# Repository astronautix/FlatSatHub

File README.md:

# Introduction

This KiCAD project is part of the Astronautix FlatSat project, which aims to create an extensible platform for nanosatellite subsystem prototyping and experimentation.

The FlatSat platform is composed of a main metallic support plate, which can possibly host 8 submodules in star configuration. Each submodule is composed of a STM32F429IDISCOVERY board and a custom adapter hat.

All modules are hooked to a central hub  (**this project**) via a sub-d DB26HD harness. The central hub has the main purpose of routing UART signals, regulating power (dispatched via sub-d, switchable) and linking all submodules together.

# The IonSat FlatSat Hub

This is the repository to host the Flatsat central hub. 

The most important task of the FlatSat hub, aside of routing the module's signals together, is being able of handling and dispatching power. 
    
Compared to the modules, this results in a slightly more complex card layout, albeit prettier. 
The multi-level schematic also gets more intricate.

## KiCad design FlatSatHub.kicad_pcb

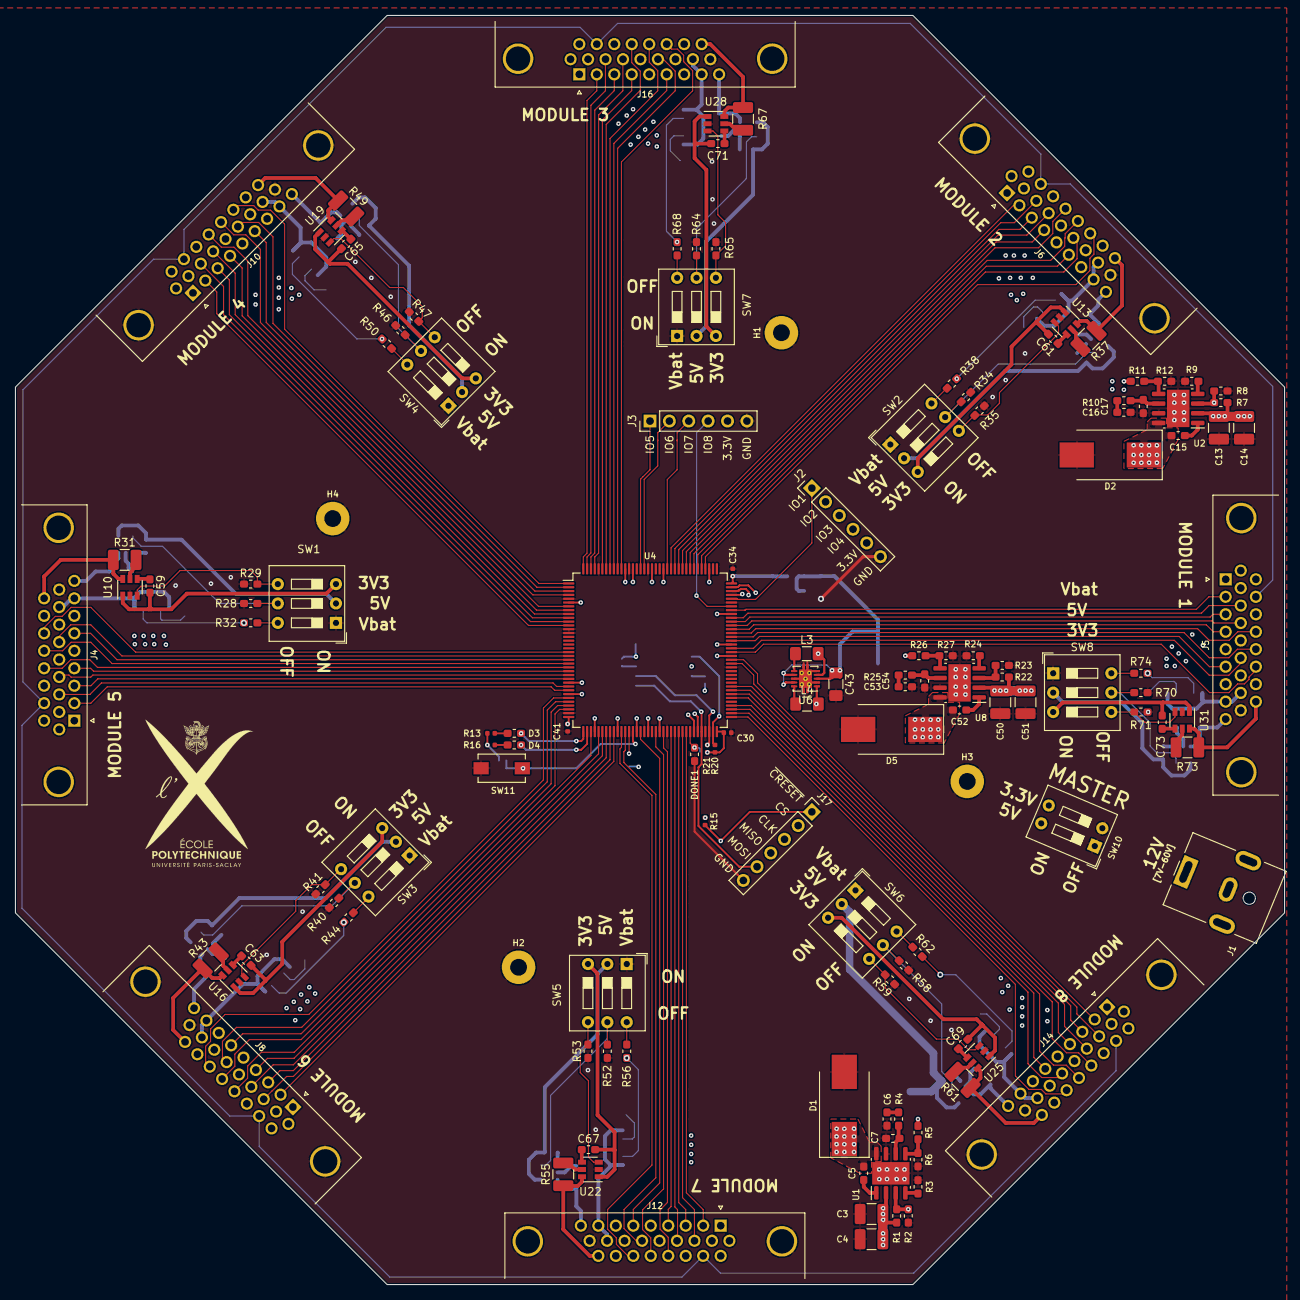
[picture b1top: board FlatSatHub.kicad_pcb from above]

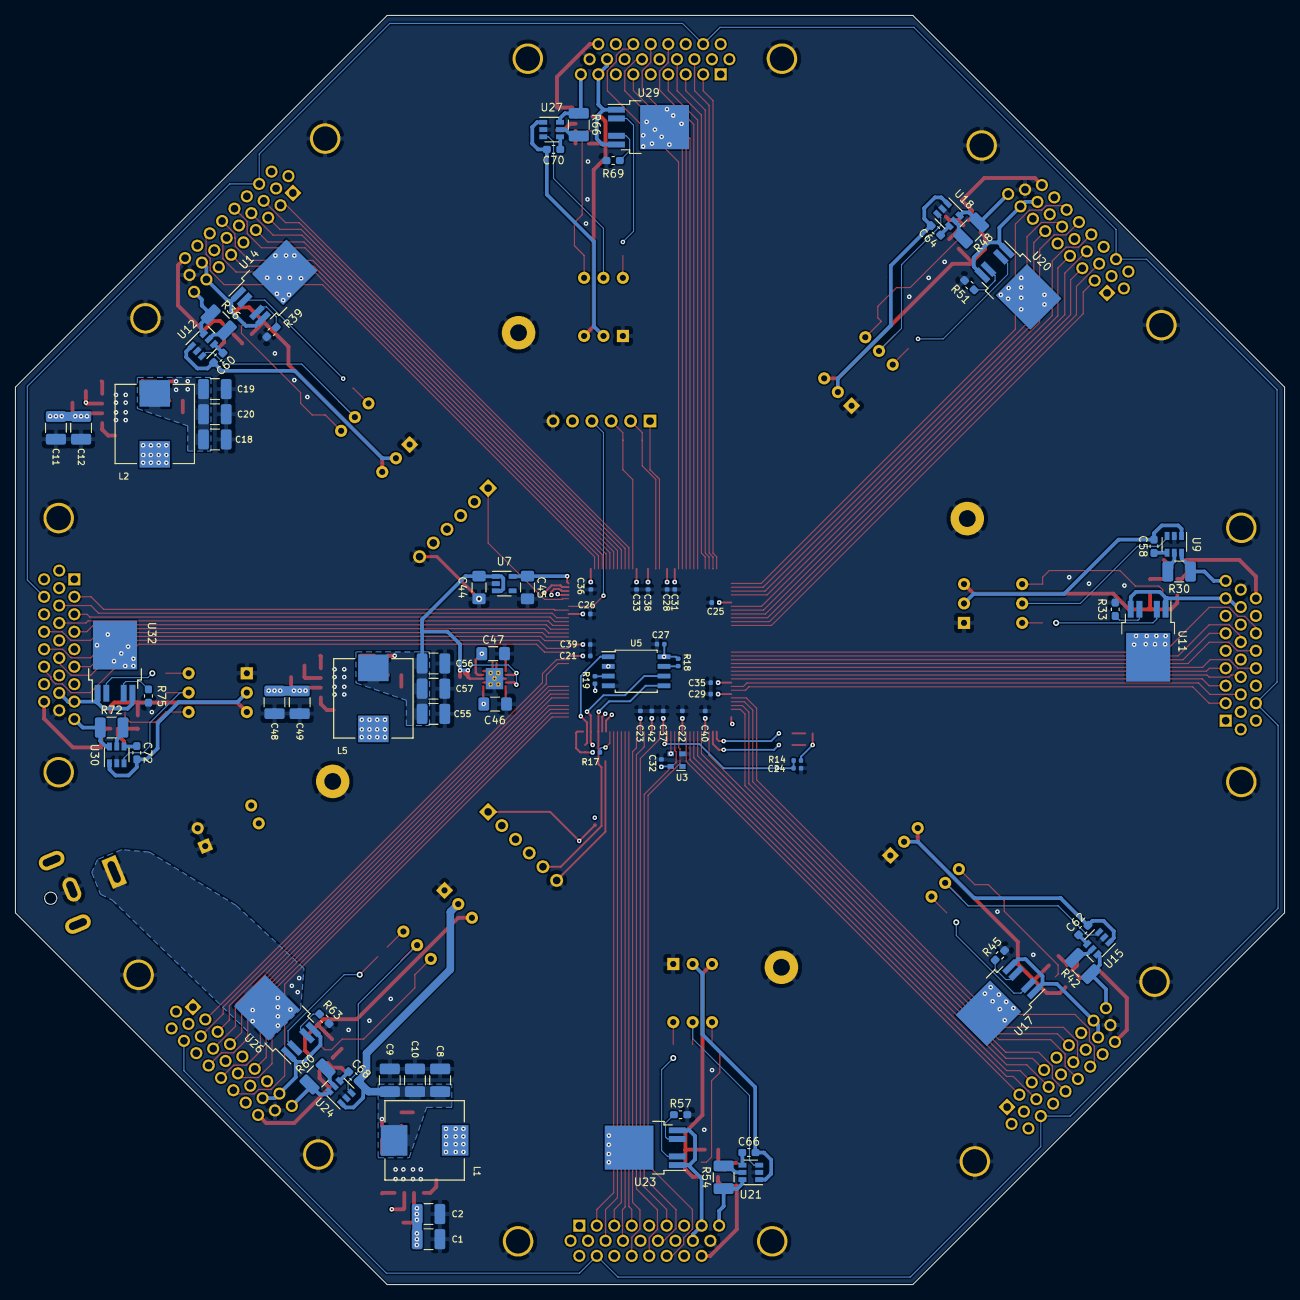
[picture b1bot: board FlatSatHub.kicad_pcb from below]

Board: 4 copper layers, 166.3 x 166.3 mm, 218 parts (88 on the bottom side), 237 nets.

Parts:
C1, C2, C3, C4, C11, C12, C13, C14, C48, C49, C50, C51: 2.2uF; C_1210_3225Metric_Pad1.42x2.65mm_HandSolder
C5, C6, C7, C15, C16, C17, C52, C53, C54, C58, C59, C60, C61, C62, C63, C64, C65, C66, C67, C68, C69, C70, C71, C72, C73: C; C_0603_1608Metric_Pad1.05x0.95mm_HandSolder
C8, C9, C10, C18, C19, C20, C55, C56, C57: 47u; C_1210_3225Metric_Pad1.42x2.65mm_HandSolder
C21, C22, C23, C24, C25, C26, C27, C28, C29, C30, C31, C32, C33, C34, C35, C36, C37, C38, C39, C40, C41, C42: 100nF; C_0402_1005Metric
C43, C44, C45, C46, C47: 10uF; C_1206_3216Metric_Pad1.42x1.75mm_HandSolder
D1, D2, D5: D_Schottky; D_SMC_Handsoldering
D3, D4: LED; R_0603_1608Metric_Pad1.05x0.95mm_HandSolder
DONE1: LED; R_0603_1608Metric_Pad1.05x0.95mm_HandSolder
H1, H2, H3, H4: MountingHole_Pad; MountingHole_2.2mm_M2_Pad
J1: Jack-DC; BarrelJack_CUI_PJ-063AH_Horizontal
J2, J3, J17: Conn_01x06; PinHeader_1x06_P2.54mm_Vertical
J4, J5, J6, J8, J10, J12, J14, J16: DB26_Male_HighDensity_MountingHoles; DSUB-26-HD_Female_Horizontal_P2.29x1.98mm_EdgePinOffset3.03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
L1, L2, L5: 7.2uH; L_Wuerth_HCI-1040
L3, L4: 2.2uH; L_1206_3216Metric_Pad1.42x1.75mm_HandSolder
LOGO1: LOGO; X-LOGO
R1, R2, R3, R4, R5, R6, R7, R8, R9, R10, R11, R12, R22, R23, R24, R25, R26, R27, R28, R29, R32, R33, R34, R35, R38, R39, R40, R41, R44, R45, R46, R47, R50, R51, R52, R53, R56, R57, R58, R59, R62, R63, R64, R65, R68, R69, R70, R71, R74, R75: R; R_0603_1608Metric_Pad1.05x0.95mm_HandSolder
R13, R14, R16, R17: 2K2; R_0402_1005Metric
R15, R18, R19, R20, R21: 10k; R_0402_1005Metric
R30, R31, R36, R37, R42, R43, R48, R49, R54, R55, R60, R61, R66, R67, R72, R73: R; R_1210_3225Metric_Pad1.42x2.65mm_HandSolder
SW1, SW2, SW3, SW4, SW5, SW6, SW7, SW8: SW_DIP_x03; SW_DIP_SPSTx03_Slide_9.78x9.8mm_W7.62mm_P2.54mm
SW10: SW_DIP_x02; SW_DIP_SPSTx02_Slide_9.78x7.26mm_W7.62mm_P2.54mm
SW11: SW_Push; SW_SPST_EVQPE1
U1, U2, U8: TPS54560B; Texas_R-PDSO-G8_EP2.95x4.9mm_Mask2.4x3.1mm
U3: ASDMB-xxxMHz; Oscillator_SMD_Abracon_ASDMB-4Pin_2.5x2.0mm
U4: ICE40HX1K-4K-TQ144; TQFP-144_20x20mm_P0.5mm
U5: M25PX32-VMW; SOIJ-8_5.3x5.3mm_P1.27mm
U6: tps6240x; Texas_S-PVSON-N10_ThermalVias
U7: TLV73325PDBV; SOT-23-5
U9, U10, U12, U13, U15, U16, U18, U19, U21, U22, U24, U25, U27, U28, U30, U31: TPS22917DBV; SOT-23-6
U11, U14, U17, U20, U23, U26, U29, U32: BTS6163D; TO-252-4

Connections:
/3.3V: C18.1, C19.1, C20.1, C59.2, C61.2, C63.2, C65.2, C67.2, C69.2, C71.2, C73.2, L2.2, R11.1, SW1.3, SW2.3, SW3.3, SW4.3, SW5.3, SW6.3, SW7.3, SW8.3, U10.1, U13.1, U16.1, U19.1, U22.1, U25.1, U28.1, U31.1
/5V: C8.1, C9.1, C10.1, C58.2, C60.2, C62.2, C64.2, C66.2, C68.2, C70.2, C72.2, L1.2, R5.1, SW1.2, SW2.2, SW3.2, SW4.2, SW5.2, SW6.2, SW7.2, SW8.2, U9.1, U12.1, U15.1, U18.1, U21.1, U24.1, U27.1, U30.1
/CAN1_RX: J4.14, J5.14, J6.14, J8.14, J10.14, J12.14, J14.14, J16.14
/CAN1_TX: J4.5, J5.5, J6.5, J8.5, J10.5, J12.5, J14.5, J16.5
/FPGA_2.5V: C34.1, C45.1, U4.108, U7.5
/I2C1_SCL: J4.19, J5.19, J6.19, J8.19, J10.19, J12.19, J14.19, J16.19
/I2C1_SDA: J4.10, J5.10, J6.10, J8.10, J10.10, J12.10, J14.10, J16.10
/I2C2_SCL: J4.20, J5.20, J6.20, J8.20, J10.20, J12.20, J14.20, J16.20
/I2C2_SDA: J4.1, J5.1, J6.1, J8.1, J10.1, J12.1, J14.1, J16.1
/MOD1_SPI1_MISO: J5.2, U4.101
/MOD1_SPI1_MOSI: J5.12, U4.99
/MOD1_SPI1_SS: J5.3, U4.98
/MOD1_SPI2_MISO: J5.13, U4.97
/MOD1_SPI2_MOSI: J5.22, U4.95
/MOD1_SPI2_SS: J5.4, U4.96
/MOD1_UART1_RX: J5.23, U4.94
/MOD1_UART1_TX: J5.15, U4.91
/MOD1_UART2_RX: J5.6, U4.93
/MOD1_UART2_TX: J5.24, U4.90
/MOD2_SPI1_MISO: J6.2, U4.121
/MOD2_SPI1_MOSI: J6.12, U4.120
/MOD2_SPI1_SS: J6.3, U4.119
/MOD2_SPI2_MISO: J6.13, U4.118
/MOD2_SPI2_MOSI: J6.22, U4.116
/MOD2_SPI2_SS: J6.4, U4.117
/MOD2_UART1_RX: J6.23, U4.115
/MOD2_UART1_TX: J6.15, U4.113
/MOD2_UART2_RX: J6.6, U4.114
/MOD2_UART2_TX: J6.24, U4.112
/MOD3_SPI1_MISO: J16.2, U4.144
/MOD3_SPI1_MOSI: J16.12, U4.143
/MOD3_SPI1_SS: J16.3, U4.142
/MOD3_SPI2_MISO: J16.13, U4.141
/MOD3_SPI2_MOSI: J16.22, U4.138
/MOD3_SPI2_SS: J16.4, U4.139
/MOD3_UART1_RX: J16.23, U4.137
/MOD3_UART1_TX: J16.15, U4.135
/MOD3_UART2_RX: J16.6, U4.136
/MOD3_UART2_TX: J16.24, U4.134
/MOD4_SPI1_MISO: J10.2, U4.12
/MOD4_SPI1_MOSI: J10.12, U4.11
/MOD4_SPI1_SS: J10.3, U4.10
/MOD4_SPI2_MISO: J10.13, U4.9
/MOD4_SPI2_MOSI: J10.22, U4.7
/MOD4_SPI2_SS: J10.4, U4.8
/MOD4_UART1_RX: J10.23, U4.4
/MOD4_UART1_TX: J10.15, U4.2
/MOD4_UART2_RX: J10.6, U4.3
/MOD4_UART2_TX: J10.24, U4.1
/MOD5_SPI1_MISO: J4.2, U4.29
/MOD5_SPI1_MOSI: J4.12, U4.28
/MOD5_SPI1_SS: J4.3, U4.26
/MOD5_SPI2_MISO: J4.13, U4.25
/MOD5_SPI2_MOSI: J4.22, U4.23
/MOD5_SPI2_SS: J4.4, U4.24
/MOD5_UART1_RX: J4.23, U4.22
/MOD5_UART1_TX: J4.15, U4.20
/MOD5_UART2_RX: J4.6, U4.21
/MOD5_UART2_TX: J4.24, U4.19
/MOD6_SPI1_MISO: J8.2, U4.45
/MOD6_SPI1_MOSI: J8.12, U4.44
/MOD6_SPI1_SS: J8.3, U4.43
/MOD6_SPI2_MISO: J8.13, U4.42
/MOD6_SPI2_MOSI: J8.22, U4.39
/MOD6_SPI2_SS: J8.4, U4.41
/MOD6_UART1_RX: J8.23, U4.34
/MOD6_UART1_TX: J8.15, U4.32
/MOD6_UART2_RX: J8.6, U4.33
/MOD6_UART2_TX: J8.24, U4.31
/MOD7_SPI1_MISO: J12.2, U4.64
/MOD7_SPI1_MOSI: J12.12, U4.63
/MOD7_SPI1_SS: J12.3, U4.62
/MOD7_SPI2_MISO: J12.13, U4.61
/MOD7_SPI2_MOSI: J12.22, U4.58
/MOD7_SPI2_SS: J12.4, U4.60
/MOD7_UART1_RX: J12.23, U4.56
/MOD7_UART1_TX: J12.15, U4.48
/MOD7_UART2_RX: J12.6, U4.52
/MOD7_UART2_TX: J12.24, U4.47
/MOD8_SPI1_MISO: J14.2, U4.88
/MOD8_SPI1_MOSI: J14.12, U4.87
/MOD8_SPI1_SS: J14.3, U4.81
/MOD8_SPI2_MISO: J14.13, U4.80
/MOD8_SPI2_MOSI: J14.22, U4.78
/MOD8_SPI2_SS: J14.4, U4.79
/MOD8_UART1_RX: J14.23, U4.76
/MOD8_UART1_TX: J14.15, U4.74
/MOD8_UART2_RX: J14.6, U4.75
/MOD8_UART2_TX: J14.24, U4.73
/SPI1_SCK: J4.11, J5.11, J6.11, J8.11, J10.11, J12.11, J14.11, J16.11
/SPI4_SCK: J4.21, J5.21, J6.21, J8.21, J10.21, J12.21, J14.21, J16.21
/Sheet5F4EF57F/Sheet5F4EF936/EN: R1.2, R2.1, SW10.4, U1.3
/Sheet5F4EF57F/Sheet5F698D24/5V: C43.1, C44.1, C55.1, C56.1, C57.1, L5.2, R26.1, U6.3, U6.7, U6.9, U7.1, U7.3
/Sheet5F4EF57F/sheet5F54C416/EN: R7.2, R8.1, SW10.3, U2.3
/Sheet5F4EF57F/sheet5F69D9D1/EN: R22.2, R23.1, U8.3
/Sheet5F604EE5/BP: C24.1, R14.2, SW11.2, U4.50
/Sheet5F604EE5/FLASH_CLK: J17.3, R21.2, U4.70, U5.6
/Sheet5F604EE5/FLASH_CS: J17.2, R20.2, U4.71, U5.1
/Sheet5F604EE5/FLASH_MISO: J17.4, U4.67, U5.2
/Sheet5F604EE5/FLASH_MOSI: J17.5, U4.68, U5.5
/Sheet5F604EE5/FLASH_~CRESET: J17.1, R15.2, U4.66
/Sheet5F604EE5/FPGA_CLK: U3.3, U4.49
/Sheet5F604EE5/IO1: J2.1, U4.104
/Sheet5F604EE5/IO2: J2.2, U4.105
/Sheet5F604EE5/IO3: J2.3, U4.106
/Sheet5F604EE5/IO4: J2.4, U4.107
/Sheet5F604EE5/IO5: J3.1, U4.129
/Sheet5F604EE5/IO6: J3.2, U4.128
/Sheet5F604EE5/IO7: J3.3, U4.122
/Sheet5F604EE5/IO8: J3.4, U4.102
/Sheet5F604EE5/LED1: D3.1, U4.37
/Sheet5F604EE5/LED2: D4.1, U4.38
/VBAT: C1.1, C2.1, C3.1, C4.1, C11.1, C12.1, C13.1, C14.1, C48.1, C49.1, C50.1, C51.1, J1.1, R1.1, R7.1, R22.1, U1.2, U2.2, U8.2, U11.3, U14.3, U17.3, U20.3, U23.3, U26.3, U29.3, U32.3
/sheet5F22A1B0/3.3V_SW: R29.2, SW1.4, U10.3
/sheet5F22A1B0/5V_SW: R28.2, SW1.5, U9.3
/sheet5F22A1B0/VBAT_SW: R32.2, SW1.6
/sheet5F22A1B0/bus_3v3: J4.26, R31.1, U10.6
/sheet5F22A1B0/bus_5v: J4.9, R30.1, U9.6
/sheet5F22A1B0/bus_vbat: J4.8, J4.17, U11.1, U11.5
/sheet5F22D1E8/3.3V_SW: R35.2, SW2.4, U13.3
/sheet5F22D1E8/5V_SW: R34.2, SW2.5, U12.3
/sheet5F22D1E8/VBAT_SW: R38.2, SW2.6
/sheet5F22D1E8/bus_3v3: J6.26, R37.1, U13.6
/sheet5F22D1E8/bus_5v: J6.9, R36.1, U12.6
/sheet5F22D1E8/bus_vbat: J6.8, J6.17, U14.1, U14.5
/sheet5F22D1E9/3.3V_SW: R41.2, SW3.4, U16.3
/sheet5F22D1E9/5V_SW: R40.2, SW3.5, U15.3
/sheet5F22D1E9/VBAT_SW: R44.2, SW3.6
/sheet5F22D1E9/bus_3v3: J8.26, R43.1, U16.6
/sheet5F22D1E9/bus_5v: J8.9, R42.1, U15.6
/sheet5F22D1E9/bus_vbat: J8.8, J8.17, U17.1, U17.5
/sheet5F66A269/3.3V_SW: R71.2, SW8.4, U31.3
/sheet5F66A269/5V_SW: R70.2, SW8.5, U30.3
/sheet5F66A269/VBAT_SW: R74.2, SW8.6
/sheet5F66A269/bus_3v3: J5.26, R73.1, U31.6
/sheet5F66A269/bus_5v: J5.9, R72.1, U30.6
/sheet5F66A269/bus_vbat: J5.8, J5.17, U32.1, U32.5
/sheet5F237BCE/3.3V_SW: R59.2, SW6.4, U25.3
/sheet5F237BCE/5V_SW: R58.2, SW6.5, U24.3
/sheet5F237BCE/VBAT_SW: R62.2, SW6.6
/sheet5F237BCE/bus_3v3: J14.26, R61.1, U25.6
/sheet5F237BCE/bus_5v: J14.9, R60.1, U24.6
/sheet5F237BCE/bus_vbat: J14.8, J14.17, U26.1, U26.5
/sheet5F237BCF/3.3V_SW: R65.2, SW7.4, U28.3
/sheet5F237BCF/5V_SW: R64.2, SW7.5, U27.3
/sheet5F237BCF/VBAT_SW: R68.2, SW7.6
/sheet5F237BCF/bus_3v3: J16.26, R67.1, U28.6
/sheet5F237BCF/bus_5v: J16.9, R66.1, U27.6
/sheet5F237BCF/bus_vbat: J16.8, J16.17, U29.1, U29.5
/sheet5F23178F/3.3V_SW: R47.2, SW4.4, U19.3
/sheet5F23178F/5V_SW: R46.2, SW4.5, U18.3
/sheet5F23178F/VBAT_SW: R50.2, SW4.6
/sheet5F23178F/bus_3v3: J10.26, R49.1, U19.6
/sheet5F23178F/bus_5v: J10.9, R48.1, U18.6
/sheet5F23178F/bus_vbat: J10.8, J10.17, U20.1, U20.5
/sheet5F231790/3.3V_SW: R53.2, SW5.4, U22.3
/sheet5F231790/5V_SW: R52.2, SW5.5, U21.3
/sheet5F231790/VBAT_SW: R56.2, SW5.6
/sheet5F231790/bus_3v3: J12.26, R55.1, U22.6
/sheet5F231790/bus_5v: J12.9, R54.1, U21.6
/sheet5F231790/bus_vbat: J12.8, J12.17, U23.1, U23.5
GND: C1.2, C2.2, C3.2, C4.2, C6.1, C7.1, C8.2, C9.2, C10.2, C11.2, C12.2, C13.2, C14.2, C16.1, C17.1, C18.2, C19.2, C20.2, C21.2, C22.2, C23.2, C24.2, C25.2, C26.2, C27.2, C28.2, C29.2, C30.2, C31.2, C32.2, C33.2, C34.2, C35.2, C36.2, C37.2, C38.2, C39.2, C40.2, C41.2, C42.2, C43.2, C44.2, C45.2, C46.2, C47.2, C48.2, C49.2, C50.2, C51.2, C53.1, C54.1, C55.2, C56.2, C57.2, D1.2, D2.2, D5.2, DONE1.1, H1.1, H2.1, H3.1, H4.1, J1.2, J2.6, J3.6, J4.0, J4.18, J5.0, J5.18, J6.0, J6.18, J8.0, J8.18, J10.0, J10.18, J12.0, J12.18, J14.0, J14.18, J16.0, J16.18, J17.6, R2.2, R3.2, R6.2, R8.2, R9.2, R12.2, R23.2, R24.2, R27.2, R28.1, R29.1, R33.1, R34.1, R35.1, R39.1, R40.1, R41.1, R45.1, R46.1, R47.1, R51.1, R52.1, R53.1, R57.1, R58.1, R59.1, R63.1, R64.1, R65.1, R69.1, R70.1, R71.1, R75.1, SW1.1, SW2.1, SW3.1, SW4.1, SW5.1, SW6.1, SW7.1, SW8.1, SW10.1, SW10.2, SW11.1, U1.7, U1.9, U2.7, U2.9, U3.2, U4.5, U4.13, U4.14, U4.35, U4.53, U4.59, U4.69, U4.86, U4.103, U4.127, U4.132, U4.140, U5.4, U6.2, U6.5, U6.8, U6.11, U7.2, U8.7, U8.9, U9.2, U10.2, U12.2, U13.2, U15.2, U16.2, U18.2, U19.2, U21.2, U22.2, U24.2, U25.2, U27.2, U28.2, U30.2, U31.2
unnamed: C5.1, D1.1, L1.1, U1.8
unnamed: C5.2, U1.1
unnamed: C6.2, R4.2
unnamed: C7.2, R4.1, U1.6
unnamed: C15.1, D2.1, L2.1, U2.8
unnamed: C15.2, U2.1
unnamed: C16.2, R10.2
unnamed: C17.2, R10.1, U2.6
unnamed: C52.1, D5.1, L5.1, U8.8
unnamed: C52.2, U8.1
unnamed: C53.2, R25.2
unnamed: C54.2, R25.1, U8.6
unnamed: C58.1, U9.4
unnamed: C59.1, U10.4
unnamed: C60.1, U12.4
unnamed: C61.1, U13.4
unnamed: C62.1, U15.4
unnamed: C63.1, U16.4
unnamed: C64.1, U18.4
unnamed: C65.1, U19.4
unnamed: C66.1, U21.4
unnamed: C67.1, U22.4
unnamed: C68.1, U24.4
unnamed: C69.1, U25.4
unnamed: C70.1, U27.4
unnamed: C71.1, U28.4
unnamed: C72.1, U30.4
unnamed: C73.1, U31.4
unnamed: D3.2, R13.2
unnamed: D4.2, R16.2
unnamed: DONE1.2, R17.2, U4.65
unnamed: L3.1, U6.6
unnamed: L4.1, U6.10
unnamed: R3.1, U1.4
unnamed: R5.2, R6.1, U1.5
unnamed: R9.1, U2.4
unnamed: R11.2, R12.1, U2.5
unnamed: R18.2, U5.7
unnamed: R19.2, U5.3
unnamed: R24.1, U8.4
unnamed: R26.2, R27.1, U8.5
unnamed: R30.2, U9.5
unnamed: R31.2, U10.5
unnamed: R32.1, U11.2
unnamed: R33.2, U11.4
unnamed: R36.2, U12.5
unnamed: R37.2, U13.5
unnamed: R38.1, U14.2
unnamed: R39.2, U14.4
unnamed: R42.2, U15.5
unnamed: R43.2, U16.5
unnamed: R44.1, U17.2
unnamed: R45.2, U17.4
unnamed: R48.2, U18.5
unnamed: R49.2, U19.5
unnamed: R50.1, U20.2
unnamed: R51.2, U20.4
unnamed: R54.2, U21.5
unnamed: R55.2, U22.5
unnamed: R56.1, U23.2
unnamed: R57.2, U23.4
unnamed: R60.2, U24.5
unnamed: R61.2, U25.5
unnamed: R62.1, U26.2
unnamed: R63.2, U26.4
unnamed: R66.2, U27.5
unnamed: R67.2, U28.5
unnamed: R68.1, U29.2
unnamed: R69.2, U29.4
unnamed: R72.2, U30.5
unnamed: R73.2, U31.5
unnamed: R74.1, U32.2
unnamed: R75.2, U32.4
VCC: C35.1, C36.1, C37.1, C38.1, C39.1, C40.1, C41.1, C42.1, C47.1, L3.2, U4.27, U4.36, U4.40, U4.51, U4.54, U4.92, U4.111, U4.126, U6.4
VCCIO_0: C21.1, C22.1, C23.1, C25.1, C26.1, C27.1, C28.1, C29.1, C30.1, C31.1, C32.1, C33.1, C46.1, J2.5, J3.5, L4.2, R13.1, R14.1, R15.1, R16.1, R17.1, R18.1, R19.1, R20.1, R21.1, U3.4, U4.6, U4.30, U4.46, U4.57, U4.72, U4.89, U4.100, U4.123, U4.131, U4.133, U5.8, U6.1

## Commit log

2020-07-10 create cutout
2020-07-16 schematic improvements
2020-07-16 add power management wiring and mounting holes
2020-07-16 create footprints
2020-07-16 First placement and autorouting
2020-07-28 rework power management schematic
2020-07-29 try improving positionning
2020-07-29 re-place footprints for symmetry
2020-07-29 minor improvements
2020-07-31 route and add documentation for schematic
2020-07-31 add markings for switchs
2020-08-03 Change DB-26-HD footprint to match what we want
2020-08-04 Rewire with new footprints
2020-08-04 fix wiring and add serigraphy
2020-08-05 new UART layout and rewire
2020-08-06 add silkscreen for uarts
2020-08-06 fix dc converter wiring and gnd track size
2020-08-06 moved vias out of the way of writings
2020-08-06 finalize
2020-09-01 Switch to female footprints and update positionning
2020-09-06 New layout with FPGA
    - Added FPGA to ease UART and SPI signals routing
    - Cleaned layout using start and circle patterns for remaining signals
    - Replaced DCDC modules with better TI components
    Missing stuff:
    - per module PSU switch
    - spare FPGA IOs connector?
2020-09-07 Most PSB done, needs more silk screen cosmetic plus review
2020-09-07 added some text, moved headers, added X logo, fixed res/diode overlap, fixed DRC
2020-09-08 Last few silk screen cleanups
2020-09-08 V1.0 (#1)
    * New layout with FPGA
    - Added FPGA to ease UART and SPI signals routing
    - Cleaned layout using start and circle patterns for remaining signals
    - Replaced DCDC modules with better TI components
    Missing stuff:
    - per module PSU switch
2020-09-11 add readme
2020-09-14 improve readme
